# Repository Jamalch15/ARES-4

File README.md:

# Modular 4DOF Arm

## Status

This repository is at an early concept stage.

The ideas described here are intentionally vague, incomplete, and subject to change. Nothing in this document set should be treated as a final architecture, final feature list, or final hardware/software split. The purpose of these docs is to capture the current direction of the project so development can start from a shared mental model.

## Early Project Overview

The project is a modular 4DOF robot arm for a mechatronics project.

At a high level, the software side is expected to cover:

- Robot motion logic such as inverse kinematics, motion sequencing, and path planning
- Vision processing, likely including YOLO or related detection pipelines
- Task-specific application logic for different robot tasks
- Communication between a host computer and an embedded controller
- A GUI for operating, tuning, calibrating, and testing the robot

## Current Working Idea

The current idea is to split computation between:

- PC side
- Embedded controller side

The rough expectation is:

- The PC handles heavy computation such as vision, task reasoning, and possibly IK/path planning
- The embedded controller handles low-level actuator control and hardware-facing behavior

This is only a working assumption. It may change once timing, reliability, and integration constraints are better understood.

## Robot Concept

The robot arm is currently expected to include:

- Two open-loop stepper-driven joints
- Two hobby-servo-driven joints
- One interchangeable end effector depending on task

Possible end effectors may include:

- Gripper
- Electromagnet
- Other task-specific tooling

The exact actuator arrangement, joint roles, coordinate conventions, and tool control interfaces are not final.

## Task-Oriented Direction

The robot is expected to perform multiple tasks. The current idea is that each task may have:

- Its own perception setup
- Its own task logic
- Its own object classes or detection targets
- Shared robot motion and control infrastructure underneath

Examples of future task types could include:

- Pick and place
- Sorting
- Object-specific handling
- Vision-guided interaction with a workspace

It is not yet decided whether each task should be a separate program, a plugin/module, or a configuration-driven mode inside one larger application.

## Documentation Map

- [AGENTS.md](AGENTS.md): guidance for coding agents working in this repository
- [pc_app/README.md](pc_app/README.md): local PC operator dashboard
- [controller_firmware/README.md](controller_firmware/README.md): ESP32-S3 firmware notes and PlatformIO commands
- `electronics/`: KiCad electronics design files
- [docs/architecture.md](docs/architecture.md): rough system architecture ideas
- [docs/component_master_plan.md](docs/component_master_plan.md): broad component planning guide
- [docs/accelerated_exam_demo_plan.md](docs/accelerated_exam_demo_plan.md): faster exam-focused demo roadmap
- [docs/physical_calibration_truth.md](docs/physical_calibration_truth.md): working DH, joint convention, TCP, and calibration-chain contract
- [docs/tasks/README.md](docs/tasks/README.md): early notes on task structure
- [docs/open_questions.md](docs/open_questions.md): unresolved decisions and design questions

## Run The Local Dashboard

The dashboard runs locally through the Python FastAPI server. From PowerShell:

```powershell
cd "C:\Users\chark\Desktop\DTU\4 Semester\Mechatronics\Mechatronics Project Files\pc_app"
.\.venv\Scripts\Activate.ps1
uvicorn app.main:app --reload --host 127.0.0.1 --port 8000
```

Keep that PowerShell window open, then visit:

```text
http://127.0.0.1:8000
```

If this is the first run, create the virtual environment and install the
dependencies first:

```powershell
cd "C:\Users\chark\Desktop\DTU\4 Semester\Mechatronics\Mechatronics Project Files\pc_app"
python -m venv .venv
.\.venv\Scripts\Activate.ps1
python -m pip install -r requirements.txt
uvicorn app.main:app --reload --host 127.0.0.1 --port 8000
```

Simulation mode is the working default, so an ESP32 does not need to be
connected just to open and inspect the dashboard.

## Stop, Restart, Or Reset Localhost

To stop localhost normally, select the PowerShell window running Uvicorn and
press `Ctrl+C`.

To restart it, stop the server and run:

```powershell
cd "C:\Users\chark\Desktop\DTU\4 Semester\Mechatronics\Mechatronics Project Files\pc_app"
.\.venv\Scripts\Activate.ps1
uvicorn app.main:app --reload --host 127.0.0.1 --port 8000
```

If port 8000 is stuck after a crash, find and stop the process using it:

```powershell
$processId = (Get-NetTCPConnection -LocalPort 8000 -State Listen).OwningProcess
Stop-Process -Id $processId
```

Then start Uvicorn again. If the browser still shows an old page, use
`Ctrl+F5` to perform a hard refresh.

To reset the app's saved machine-specific settings, stop the server and rename
the local config:

```powershell
cd "C:\Users\chark\Desktop\DTU\4 Semester\Mechatronics\Mechatronics Project Files\pc_app"
Move-Item .\config\robot.local.yaml .\config\robot.local.backup.yaml
```

Start the server again. The app will fall back to the tracked,
simulation-safe `config/robot.example.yaml`. This resets saved calibration,
hardware IO, tool, camera, and other local settings; keep the backup if those
values may be needed later.

More startup and troubleshooting details are in
[pc_app/README.md](pc_app/README.md).

## GitHub And Local Files

The intended GitHub repository name is `modular-4dof-arm`.

Tracked configuration should stay generic. Machine-specific calibration and
hardware values belong in `pc_app/config/robot.local.yaml`, which is ignored by
Git. The tracked `pc_app/config/robot.example.yaml` remains the template and
simulation-safe fallback.

## Intended Use Of These Docs

These docs are here to:

- Capture current intent before details are forgotten
- Give future contributors and agents a shared starting point
- Make assumptions explicit
- Leave room for the design to evolve without pretending decisions are final

If a future implementation conflicts with these notes, the implementation or updated design discussion should take priority over outdated assumptions in these early docs.

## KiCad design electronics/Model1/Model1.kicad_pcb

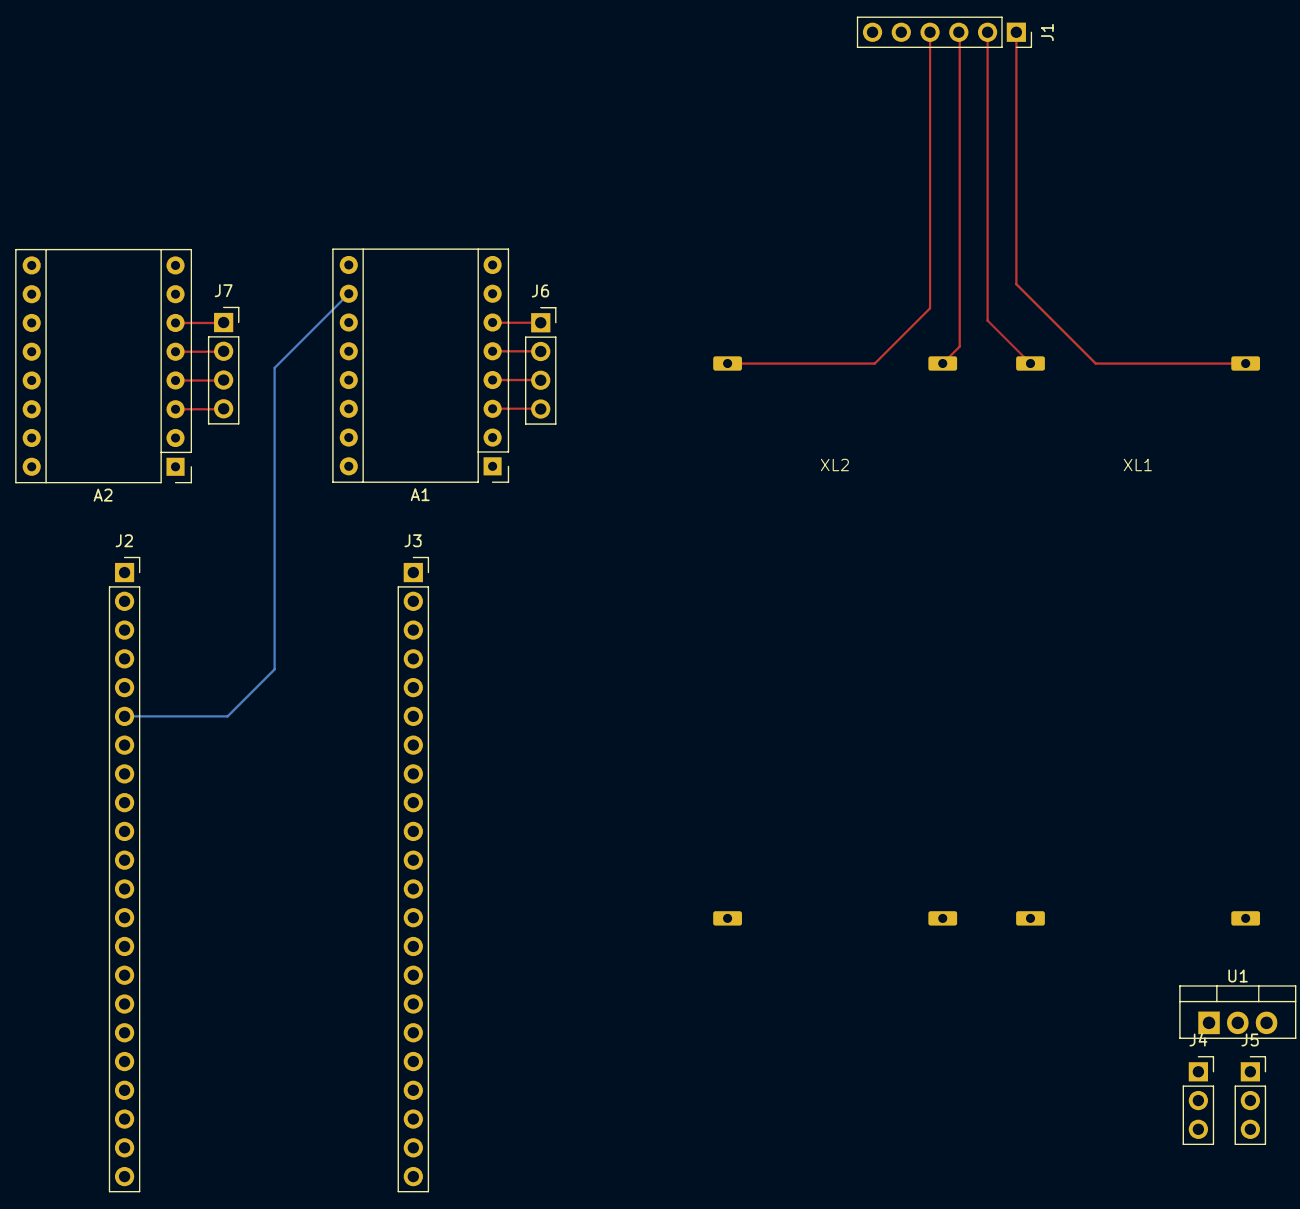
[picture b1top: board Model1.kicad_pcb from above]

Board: 2 copper layers, 12 parts (0 on the bottom side), 30 nets.

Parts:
A1, A2: Pololu_Breakout_DRV8825; Pololu_Breakout-16_15.2x20.3mm
J1: Conn_01x06_Pin; PinSocket_1x06_P2.54mm_Vertical
J2, J3: Conn_01x22_Socket; PinSocket_1x22_P2.54mm_Vertical
J4, J5: Conn_01x03_Pin; PinSocket_1x03_P2.54mm_Vertical
J6, J7: Conn_01x04_Pin; PinSocket_1x04_P2.54mm_Vertical
U1: LM7805_TO220; TO-220-3_Vertical
XL1, XL2: XL4015_Module_THT

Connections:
unnamed: A1.4 (A1), J6.3
unnamed: A1.3 (A2), J6.4
unnamed: A1.5 (B1), J6.2
unnamed: A1.6 (B2), J6.1
unnamed: A1.16 (DIR), J2.7
unnamed: A1.10 (M0), J2.6
unnamed: A1.11 (M1), J2.5
unnamed: A1.12 (M2), J2.4
unnamed: A1.15 (STEP), J2.8
unnamed: A1.8 (VMOT), A2.8 (VMOT), J1.5
unnamed: A1.13 (~RST), A1.14 (~SLP), A2.13 (~RST), A2.14 (~SLP), J2.1
unnamed: A2.4 (A1), J7.3
unnamed: A2.3 (A2), J7.4
unnamed: A2.5 (B1), J7.2
unnamed: A2.6 (B2), J7.1
unnamed: A2.16 (DIR), J2.12
unnamed: A2.10 (M0), J2.11
unnamed: A2.11 (M1), J2.10
unnamed: A2.12 (M2), J2.9
unnamed: A2.15 (STEP), J2.13
unnamed: J1.1, XL1.1 (IN+)
unnamed: J1.2, XL1.2 (In-)
unnamed: J1.3, XL2.1 (IN+)
unnamed: J1.4, XL2.2 (In-)
unnamed: A1.1 (GND), A1.7 (GND), A2.1 (GND), A2.7 (GND), J1.6, J3.1, J4.2, J5.2, U1.2 (GND), XL1.4 (OUT-), XL2.4 (OUT-)
unnamed: J2.21, U1.3 (VO)
unnamed: J3.4, J5.1
unnamed: J3.5, J4.1
unnamed: J4.3, XL1.3 (OUT+)
unnamed: J5.3, U1.1 (VI), XL2.3 (OUT+)

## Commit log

2026-06-15 Initial Modular 4DOF Arm project
2026-06-16 Professionalize arm dashboard roadmap and controls
2026-06-16 Regroup remaining implementation roadmap
2026-06-16 Align robot model with DH geometry convention
2026-06-16 Add TestClient dependency for CI
2026-06-16 Show measured base support lengths in robot view
2026-06-16 Attach L3 support to L2 bend in robot view
2026-06-16 Make L2 active in measured DH convention
2026-06-16 Draw DH joint hubs as axis cylinders
2026-06-16 Model L2 as side offset in kinematics
2026-06-16 Smooth servo motion and apply UI limits
2026-06-18 Add Cartesian jog, trajectory, and camera calibration workflows
    Implement continuous Cartesian live jogging with bounded differential IK, JOGV streaming, explicit failure reasons, clean stop/restart lifecycle handling, and regression diagnostics.
    Add timed trajectory upload and controller-side following, expanded motion diagnostics, branch-continuity improvements, and protocol/firmware support for JOGV, JOG STOP, and TRAJ commands.
    Add AprilTag camera calibration, persistence, verification, robot-frame projection, viewport overlays, CLI tooling, and the camera settings analysis.
    Expand the operator UI and settings model for path tuning, robot geometry, camera calibration, tool configurati
2026-06-18 Make motion tests independent of local calibration
    Use the tracked example robot model for geometry-sensitive Cartesian jog and IK continuity tests, assert continuity by joint distance instead of solver seed labels, and account for saved path-default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
2026-06-18 Revamp vision calibration and Cartesian jog pipeline
    Replace the ad hoc camera workflow with a planar-first workspace calibration pipeline based on square fiducials. Add shared ArUco/AprilTag detection, saved/live homography handling, workspace masking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
    Add a bounded Cartesian servo path for live jog commands, wire SERVOJ protocol support through the PC app and ESP32 firmware/stub, and update motion diagnostics and tests around deterministic jog beh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
    Update dashboard settings, camera calibration UI, object/task panels, version/resta
2026-06-19 Refine saved workspace calibration and fix CI
    Replace live recalibration with a one-shot workspace calibration command that collects stable tag observations, validates outer-corner and tag-center geometry, and automatically persists only accepte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
    Use the saved planar homography for normal robot coordinates and a dedicated compressed live workspace projection endpoint. Update the Three.js texture in place for a faster viewport feed without req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
    Simplify Camera Settings to calibrate and verify controls, remove the redundant camera save and live settings preview, keep color detection in Tasks, and stop task camera polling when leaving Tasks.
    Make optional 6-DoF
2026-06-20 Refine calibration and task workflows
2026-06-20 Implement WP-03 calibration truth
2026-06-20 Complete WP-04 motion contract reporting
2026-06-20 Add program library and refine operator workflows
2026-06-21 Extend calibration and task execution workflows
2026-06-23 Add manual shoulder encoder alignment
2026-06-23 Snapshot encoder integration work
2026-06-23 Fix task preview state and IK encoder correction
2026-06-23 Handle post-correction shoulder residuals
2026-06-23 Relax encoder rebase for correction deadband
2026-06-24 Smooth shoulder motion and add viewport ESP sync
